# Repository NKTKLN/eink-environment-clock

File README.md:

# 🌱 E-Ink Environment Clock

**E-Ink Environment Clock** is a desk clock on an ESP32-C3 with a 2.9" e-paper panel that shows the time next to indoor CO₂, temperature, humidity and pressure. It is set up from its own web page, publishes its readings to Home Assistant over MQTT and has a local JSON API with no account or key.

The clock has no buttons and no screen you can type on, and it has to stay a clock when the network is gone. So everything is configured from a phone: with no saved network it opens a WPA2 access point and prints the name, password and a QR code on the panel. When a known network disappears it keeps showing the time from its RTC and puts the access point details in a strip at the bottom instead of taking over the screen. The panel itself is slow and ghosts, so it is redrawn only when something visible changes.

## 📦 Dependencies

| Needed for | What | Install |
| --- | --- | --- |
| Building and flashing | [PlatformIO Core](https://docs.platformio.org/en/latest/core/installation/index.html); it downloads ESP-IDF 5.5 and the toolchain itself | `pipx install platformio` |
| Host tests | A C compiler (`gcc` or `clang`) | your package manager |
| Releases | [Commitizen](https://commitizen-tools.github.io/commitizen/), configured in `.cz.toml` | `pipx install commitizen` |

Sensor drivers come from the ESP Component Registry on the first build ([esp-idf-lib](https://esp-idf-lib.readthedocs.io/) `bmp280`, `ds3231`, `mhz19b`, plus `espressif/mdns`).

## 🔩 Hardware

| Part | Model | ESP32-C3 pins |
| --- | --- | --- |
| Microcontroller | ESP32-C3 Super Mini, 4 MB flash | — |
| Display | WeAct Studio 2.9" B/W e-paper, SSD1680, 296×128 | SCK 4, MOSI 6, CS 7, DC 2, RST 3, BUSY 10 |
| Temperature, humidity, pressure | BME280 (BMP280 works without humidity) | I²C SDA 8, SCL 9 |
| Real-time clock | DS3231 | I²C SDA 8, SCL 9 |
| CO₂ | MH-Z19 | UART RX 5 ← sensor TX, TX 1 → sensor RX |
| Status LED | — | 0 |

The pins live in `firmware/src/app_config.h`. GPIO 9 is the BOOT button on the Super Mini and is taken by I²C, which is why the reset below works through power cycles rather than a button.

## 🚀 Flashing

The partition table has two OTA slots and an NVS partition for settings.

> [!IMPORTANT]
> When the board still runs firmware with the old single-app partition table, erase the flash once before the first upload. Later uploads keep the settings.

```sh
cd firmware && pio run -t erase
```

Build and flash over the native USB, then watch the log:

```sh
cd firmware && pio run -t upload && pio device monitor
```

After that, updates go over the air: from GitHub releases or by uploading `.pio/build/esp32-c3-supermini/firmware.bin` on the **System** tab. If a new image fails to start, the bootloader returns to the previous one.

## 📶 Wi-Fi setup

| Situation | What the clock does |
| --- | --- |
| No saved network | Opens the access point `EinkClock-XXXX` and shows the setup screen |
| Saved network unreachable for 30 s | Opens the access point and keeps retrying the saved network; the clock face stays, with the access point details in a strip at the bottom |
| Connected | Shows its address at the bottom for 30 seconds (adjustable, or until removed); the access point stops one minute after connecting |

The access point is WPA2 with a fresh 8-digit password every time it starts, because it also comes up after power cuts when the router boots slower than the clock, and an open network would let anyone nearby point the clock at their own broker. The panel shows the network name, password, a Wi-Fi QR code and `192.168.4.1`. Phones open the setup page on their own: a small DNS server answers every name with that address.

To forget the Wi-Fi and MQTT settings without the web page, plug the clock in three times in a row, unplugging it within five seconds each time. Only power-on resets count, so restarts after an update or a crash never trigger it.

## 🖥️ Web interface

Open `http://<clock-ip>/` or `http://eink-clock-<id>.local/`. English and Russian, light and dark theme, works on a phone. The page is gzipped into the firmware and loads nothing from the internet, so it also works over the setup access point.

| Tab | Contents |
| --- | --- |
| Overview | What the panel shows now, readings, a message for the screen, status |
| Display | Layout, which readings appear and in which order, date and time format, time zone, units, white on black, upside down; a preview rendered by the clock before saving |
| Network | Wi-Fi scan and connection, MQTT broker |
| System | Name, CO₂ threshold, temperature correction, CO₂ calibration, firmware updates, restart and reset |
| Developer | Live device log, log level, API console, raw state |

There is no password on the web interface: it is meant for a home network.

## 🖼️ Screen

| Layout | What it shows |
| --- | --- |
| `classic` | Time and date on the left, enabled readings in a column on the right |
| `clock` | Time and date across the whole panel |
| `co2` | CO₂ in large digits, time and the other readings in a row below |
| `sensors` | Enabled readings in a grid, no clock |

Disabled readings free their space: the column re-centres, one reading is drawn large, and with none left the clock takes the full width. A CO₂ value above the threshold is drawn white on black.

Messages appear as a black strip along the bottom (one line in large type or two in small, cut with "…"), or across the whole panel with `fullscreen`. They can expire after a set time. The panel font is the classic 5×7 bitmap font with Cyrillic letters drawn on the same grid (`firmware/tools/gen_cyrillic_font.py`).

Refresh policy, against ghosting: a full refresh on boot and whenever the kind of screen changes, a partial refresh when the content changes but not more often than every 10 seconds, and a forced full refresh after 10 partial ones.

## 🏠 Home Assistant

Turn on MQTT on the **Network** tab and point it at the broker Home Assistant uses. The clock announces itself through device-based MQTT discovery (Home Assistant 2024.11 or newer) and appears as one device without any YAML.

| Entity | Type |
| --- | --- |
| Temperature, humidity, pressure, CO₂, Wi-Fi signal, uptime | `sensor` |
| CO₂ above threshold | `binary_sensor` |
| Permanent notification, temporary notification | `text` |
| Clear message, restart, calibrate CO₂ | `button` |
| Screen layout | `select` |
| CO₂ threshold, temporary notification time (minutes) | `number` |

There are two kinds of messages. A permanent one stays on the screen until it is removed with the button, from the web interface or through the API. A temporary one disappears by itself: Home Assistant shows it for the time set in its `number` entity, and the web interface asks for the time next to the text.

Readings are published every 30 seconds, and the state right after a setting or a message changes. Automations can set the time per message, or show it on the full screen, through `eink-clock/<id>/notify` (`ttl` 0 means permanent):

```yaml
action: mqtt.publish
data:
  topic: eink-clock/a1b2c3/notify
  payload: '{"text": "Open the window", "ttl": 600, "fullscreen": true}'
```

| Topic under `eink-clock/<id>/` | Direction | Payload |
| --- | --- | --- |
| `state` | out | JSON with all readings, retained |
| `status` | out | `online` / `offline` (last will) |
| `notify` | in | `{"text", "ttl", "fullscreen"}` or plain text |
| `notification/set` | in | plain text, permanent |
| `notification_temp/set` | in | plain text, temporary |
| `notification_time/set` | in | minutes for temporary text, 1…10080 |
| `command` | in | `clear_notification`, `reboot`, `calibrate_co2` |
| `layout/set` | in | `classic`, `clock`, `co2`, `sensors` |
| `co2_threshold/set` | in | 400…5000 |

## ⬆️ Updates and releases

CI publishes a release for every version tag: it builds the firmware with the tag as its version and attaches `firmware.bin`. Tags follow the commitizen format in `.cz.toml` (`1.2.0`, no `v`); a tag with a `-` becomes a pre-release, which the clock does not offer.

```sh
cz bump && git push --follow-tags
```

The clock asks the GitHub API for the latest release once a day and offers it on the **System** tab with its notes and an **Install** button. With automatic updates turned on, a newer release is installed between 03:00 and 05:00 local time, and never while the clock does not know the time. Downloads go over HTTPS with the ESP-IDF certificate bundle.

Images are not signed: HTTPS proves the file came from GitHub, not who uploaded it. Anyone who can publish releases in this repository can ship firmware to clocks with automatic updates on.

Local builds take their version from `.cz.toml`, so a board flashed from the same commit as the latest release does not offer to "update" to it.

## 🔧 Configuration

Everything below is changed in the web interface or with `POST /api/config` (a partial object is enough) and stored in NVS as JSON. Settings survive updates: OTA writes only the app slots, keys the old firmware did not know get their defaults, unknown keys are ignored. CI fails if the NVS partition is moved in `partitions.csv`, because that would wipe them.

| Key | Default | What it is |
| --- | --- | --- |
| `name` | `E-Ink Clock` | Device name, also in Home Assistant |
| `display.language` | `en` | Screen language, `en` or `ru` |
| `display.hour24` | `false` | 24-hour time; the original firmware used 12-hour |
| `display.timezone`, `display.tz_posix` | `Europe/Moscow`, `MSK-3` | Shown name and the POSIX TZ string the firmware uses |
| `display.date_format` | `dmy_text` | `dmy_text` (3 Nov 2026), `weekday`, `dmy_dots`, `iso` |
| `display.show_date` | `true` | Date under the time |
| `display.layout` | `classic` | See the Screen section |
| `display.metrics` | all four, in order | Which readings appear and in which order |
| `display.invert`, `display.rotate180` | `false` | White on black, upside down |
| `display.temp_unit`, `display.pressure_unit` | `c`, `hpa` | Also `f`, `mmhg` |
| `sensors.temp_offset_c` | `-2.3` | Added to the BME280 reading, carried over from the original firmware; limited to ±10 °C |
| `sensors.co2_threshold_ppm` | `1000` | CO₂ alarm: inverted value, LED, Home Assistant binary sensor |
| `sensors.co2_led` | `true` | Blink the LED above the threshold |
| `mqtt.enabled`, `mqtt.host`, `mqtt.port` | `false`, empty, `1883` | Broker; the host may also be a full `mqtt://` URI; TLS (`mqtts://`) is not set up |
| `mqtt.username`, `mqtt.password` | empty | Broker login; the API never returns the password |
| `mqtt.prefix` | empty = `eink-clock/<id>` | Topic prefix |
| `mqtt.discovery`, `mqtt.discovery_prefix` | `true`, `homeassistant` | Home Assistant discovery |
| `update.check` | `true` | Look for a new release once a day |
| `update.auto` | `false` | Install new releases at night; off by default so nothing changes on a clock without the owner asking |

Wi-Fi credentials are set through `POST /api/wifi`, which also reconnects. Fixed timings (sensor interval 30 s, SNTP every 30 minutes, the Wi-Fi fallback above, display refresh limits) are in `firmware/src/app_config.h`.

## 🔌 HTTP API

No keys and no accounts. Everything is JSON except the screen images. CORS is open, so a page or script on another host can call it.

| Method | Path | Purpose |
| --- | --- | --- |
| `GET` | `/api/state` | Readings, time, Wi-Fi, MQTT, message, device info |
| `GET` / `POST` | `/api/config` | Settings; `POST` takes a partial object |
| `GET` | `/api/screen.bmp` | What the panel shows now |
| `POST` | `/api/preview` | Renders unsaved settings, returns a BMP |
| `POST` / `DELETE` | `/api/notify` | Show or clear a message |
| `GET` | `/api/wifi/scan` | Nearby networks |
| `POST` | `/api/wifi` | Save a network and connect |
| `POST` | `/api/co2/calibrate` | MH-Z19 zero point (400 ppm) |
| `POST` | `/api/ota` | Firmware image as the request body |
| `GET` | `/api/update` | Running and latest release, install progress |
| `POST` | `/api/update/check`, `/api/update/install` | Check GitHub now, install the latest release |
| `GET` | `/api/logs?since=N` | Device log after position `N` |
| `POST` | `/api/log-level` | `{"level": "debug", "tag": "*"}` |
| `POST` | `/api/system/reboot`, `/api/system/forget-wifi`, `/api/system/factory-reset` | Maintenance |

Show a message on the screen for an hour:

```sh
curl -X POST http://192.168.1.42/api/notify -d '{"text": "Meeting until 15:00", "ttl": 3600}'
```

## 🛠️ Developer tools

The **Developer** tab keeps the last 12 KB of the device log since boot in RAM and shows it live, with filters by level and text and a download button. It can change the log level per tag until the next restart, send any request to the API and show the raw `/api/state`. The same log is on the USB console via `pio device monitor`.

## 🧪 Tests

Everything that does not touch hardware is plain C and runs on the host: settings and their JSON, settings from older and newer firmware, layouts and text wrapping, the Cyrillic font, messages and their expiry, the power-cycle reset, captive-portal DNS replies, MQTT payloads and commands, version comparison and GitHub release parsing, the log ring buffer. That is 60 test cases. They use cJSON from the ESP-IDF package, so build the firmware once first.

```sh
cd firmware && pio test -e native
```

Set `PREVIEW_DIR` to get every screen the tests render as a PBM image:

```sh
cd firmware && PREVIEW_DIR=/tmp/screens pio test -e native -f test_ui
```

A passing suite says the logic and the drawing are right. It says nothing about Wi-Fi, the radio, the panel driver, the sensors or OTA, which only run on the board. CI runs the build and the tests on every push.

## 🧩 PCB

The KiCad project is in `pcb/eink-environment-clock/`, Gerber files in `pcb/pcb/`. Reference images:

```
images/
├── assembled_board_image.png
├── circuit_image.png
├── pcb_back_image.png
├── pcb_front_image.png
└── schematic_image.png
```

## 🧰 Case

```
3d_model/
├── stp
│   ├── backplate.stp
│   ├── center.stp
│   └── frontplate.stp
├── case.3mf
└── case.m3d
```

## ⚠️ Known issues

* Holes for the **MH-Z19** are too small.
* Some modules (**MH-Z19**) sit too close to the mounting holes, which makes assembly and fastening inconvenient.

## 📁 Source layout

```
firmware/
├── platformio.ini        # firmware env and the host test env
├── partitions.csv        # NVS + two OTA slots
├── web/index.html        # web interface, gzipped into the image at build time
├── test/                 # host unit tests
├── tools/                # web embedding, cJSON for tests, Cyrillic glyph generator
└── src/
    ├── app_main.c        # main loop: sensors, screen choice, refresh policy
    ├── app_config.h      # pins, timings, update repository
    ├── settings*.c       # settings, JSON <-> NVS
    ├── wifi_mgr.c        # station, setup access point, mDNS
    ├── dns_*.c           # captive-portal DNS
    ├── web_server.c      # HTTP API, preview, OTA, logs
    ├── mqtt_ha.c         # MQTT client; ha_*.c build and parse its messages
    ├── updater.c         # GitHub release check and install; release.c parses
    ├── log_*.c           # log capture into a RAM ring buffer
    ├── ui.c              # layouts, messages, setup and system screens
    ├── epd_canvas.c      # 1-bit canvas, UTF-8 text, fonts
    ├── epd_ssd1680.c     # e-paper driver
    └── third_party/      # QR Code generator (Project Nayuki, MIT)
```

The e-paper driver follows the panel vendor's reference code from [WeActStudio.EpaperModule](https://github.com/WeActStudio/WeActStudio.EpaperModule).

## 📜 License

[MIT](./LICENSE).

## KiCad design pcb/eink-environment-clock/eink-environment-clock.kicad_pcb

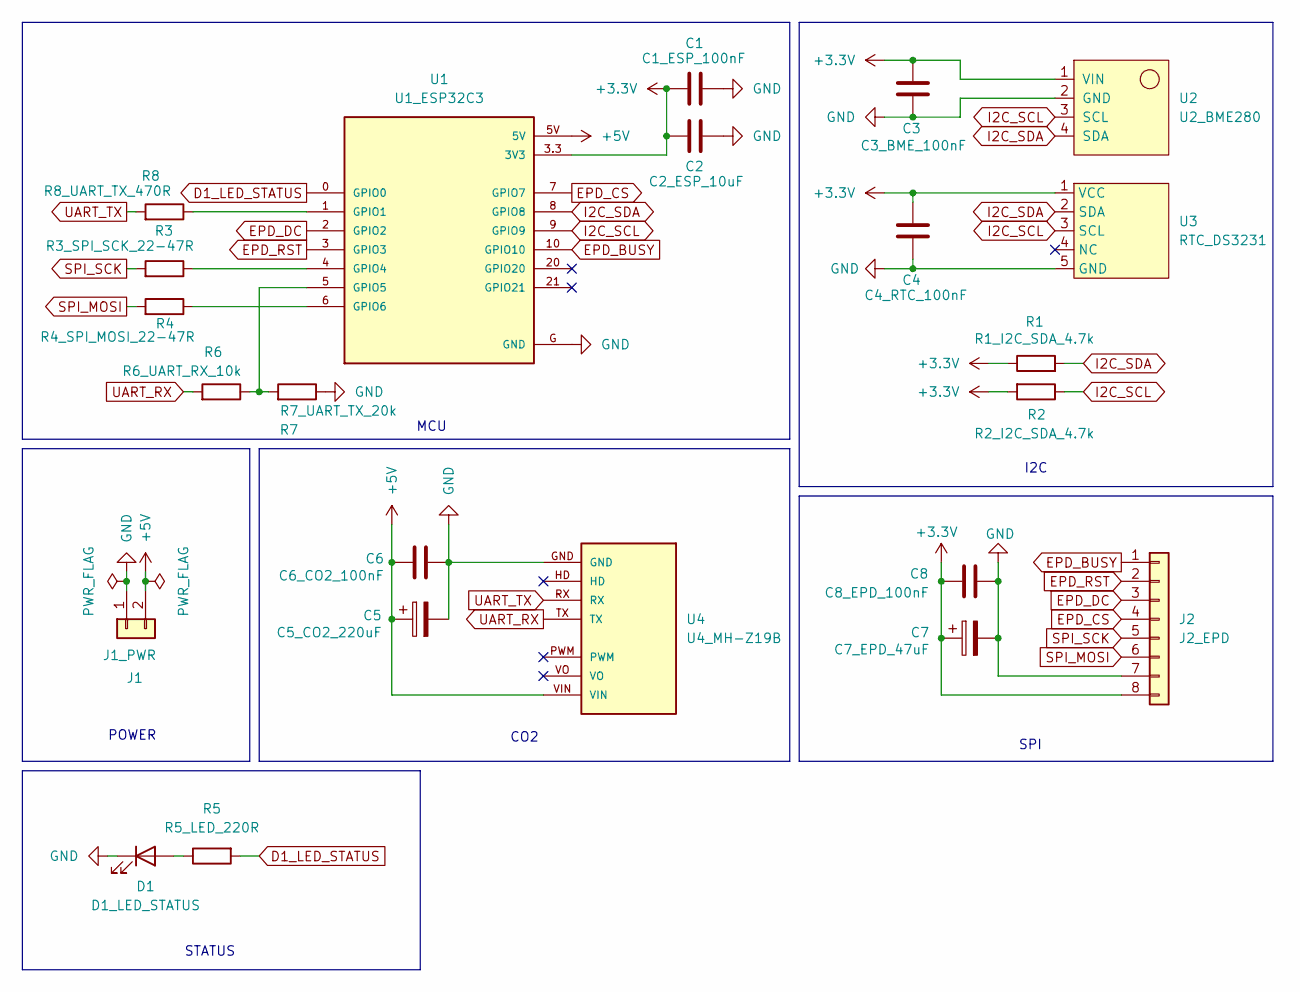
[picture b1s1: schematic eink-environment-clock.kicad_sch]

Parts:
C1: C1_ESP_100nF; C_Disc_D5.0mm_W2.5mm_P2.50mm
C2: C2_ESP_10uF; C_Disc_D5.0mm_W2.5mm_P2.50mm
C3: C3_BME_100nF; C_Disc_D5.0mm_W2.5mm_P2.50mm
C4: C4_RTC_100nF; C_Disc_D5.0mm_W2.5mm_P2.50mm
C5: C5_CO2_220uF; CP_Radial_D8.0mm_P3.50mm
C6: C6_CO2_100nF; C_Disc_D5.0mm_W2.5mm_P2.50mm
C7: C7_EPD_47uF; CP_Radial_D6.3mm_P2.50mm
C8: C8_EPD_100nF; C_Disc_D5.0mm_W2.5mm_P2.50mm
D1: D1_LED_STATUS; LED_D5.0mm
J1: J1_PWR; JST_PH_B2B-PH-K_1x02_P2.00mm_Vertical
J2: J2_EPD; JST_PH_B8B-PH-K_1x08_P2.00mm_Vertical
R1: R1_I2C_SDA_4.7k; R_Axial_DIN0207_L6.3mm_D2.5mm_P7.62mm_Horizontal
R2: R2_I2C_SDA_4.7k; R_Axial_DIN0207_L6.3mm_D2.5mm_P7.62mm_Horizontal
R3: R3_SPI_SCK_22-47R; R_Axial_DIN0207_L6.3mm_D2.5mm_P7.62mm_Horizontal
R4: R4_SPI_MOSI_22-47R; R_Axial_DIN0207_L6.3mm_D2.5mm_P7.62mm_Horizontal
R5: R5_LED_220R; R_Axial_DIN0207_L6.3mm_D2.5mm_P7.62mm_Horizontal
R6: R6_UART_RX_10k; R_Axial_DIN0207_L6.3mm_D2.5mm_P7.62mm_Horizontal
R7: R7_UART_TX_20k; R_Axial_DIN0207_L6.3mm_D2.5mm_P7.62mm_Horizontal
R8: R8_UART_TX_470R; R_Axial_DIN0207_L6.3mm_D2.5mm_P7.62mm_Horizontal
U1: U1_ESP32C3; MODULE_ESP32-C3_SUPERMINI_TH
U2: U2_BME280; module_bme280_alt
U3: RTC_DS3231; DS3231_For_Pi
U4: U4_MH-Z19B; MH-Z19B

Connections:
+3.3V: C1.2, C2.2, C3.1, C4.1, C7.1, C8.2, J2.8, R1.1, R2.2, U1.3.3 (3V3), U2.1 (VIN), U3.1 (VCC)
+5V: C5.1, C6.2, J1.2, U1.5V, U4.VIN
D1_LED_STATUS: R5.2, U1.0 (GPIO0)
EPD_BUSY: J2.1, U1.10 (GPIO10)
EPD_CS: J2.4, U1.7 (GPIO7)
EPD_DC: J2.3, U1.2 (GPIO2)
EPD_RST: J2.2, U1.3 (GPIO3)
GND: C1.1, C2.1, C3.2, C4.2, C5.2, C6.1, C7.2, C8.1, D1.1 (K), J1.1, J2.7, R7.1, U1.G (GND), U2.2 (GND), U3.5 (GND), U4.GND
I2C_SCL: R2.1, U1.9 (GPIO9), U2.3 (SCL), U3.3 (SCL)
I2C_SDA: R1.2, U1.8 (GPIO8), U2.4 (SDA), U3.2 (SDA)
unnamed: D1.2 (A), R5.1
unnamed: R8.1, U1.1 (GPIO1)
unnamed: R3.1, U1.4 (GPIO4)
unnamed: R6.1, R7.2, U1.5 (GPIO5)
unnamed: R4.1, U1.6 (GPIO6)
SPI_MOSI: J2.6, R4.2
SPI_SCK: J2.5, R3.2
UART_RX: R6.2, U4.TX
UART_TX: R8.2, U4.RX

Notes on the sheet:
POWER
CO2
SPI
I2C
STATUS
MCU

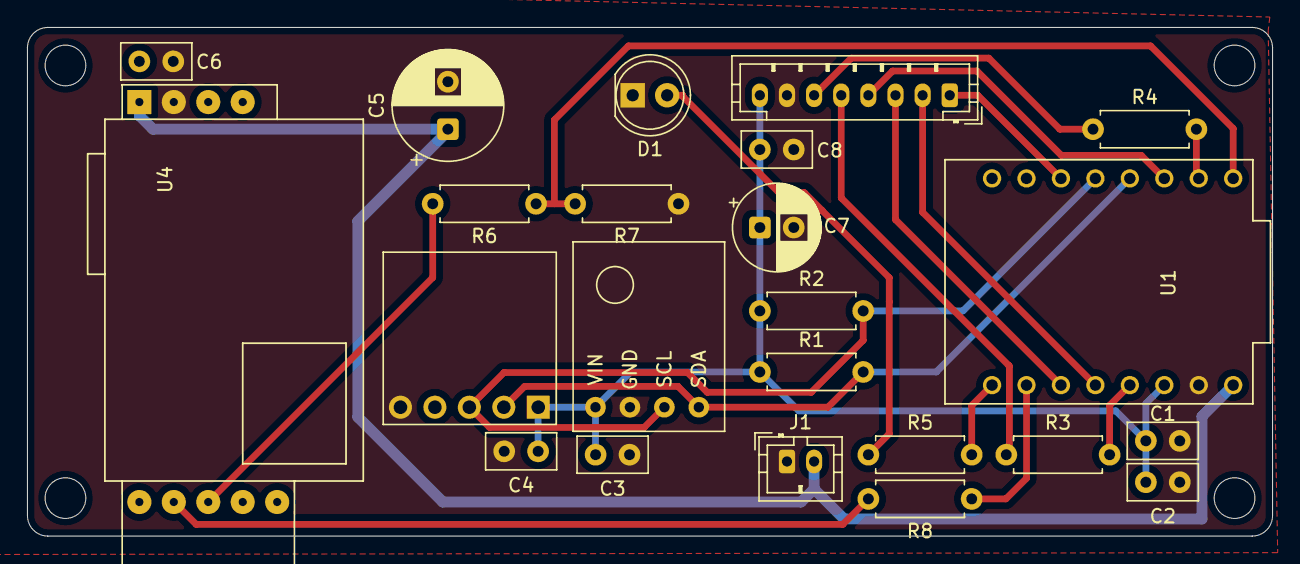
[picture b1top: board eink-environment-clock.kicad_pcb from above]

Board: 2 copper layers, 91.8 x 37.5 mm, 23 parts (0 on the bottom side), 19 nets.

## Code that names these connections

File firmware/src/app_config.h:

#pragma once

/* =====================================================
 * Pin configuration (ESP32-C3 Super Mini)
 * ===================================================== */

/* E-paper display (SPI) */
#define PIN_EPD_DC   2
#define PIN_EPD_RST  3
#define PIN_SPI_SCK  4
#define PIN_SPI_MOSI 6
#define PIN_EPD_CS   7
#define PIN_EPD_BUSY 10

/* I2C bus (BME280 + DS3231) */
#define PIN_I2C_SDA 8
#define PIN_I2C_SCL 9

/* MH-Z19 UART (ESP RX <- sensor TX, ESP TX -> sensor RX) */
#define PIN_MHZ_RX 5
#define PIN_MHZ_TX 1

/* Status LED */
#define PIN_LED 0

/* =====================================================
 * Fixed configuration. Everything a user may want to change (time zone,
 * 12/24 h, units, CO2 threshold, Wi-Fi, MQTT, ...) lives in settings.c and
 * is edited through the web interface.
 * ===================================================== */

#define NTP_SERVER "pool.ntp.org"

/* Firmware updates: GitHub releases of this repository, asset name. */
#define UPDATE_REPO  "NKTKLN/eink-environment-clock"
#define UPDATE_ASSET "firmware.bin"

#define SENSOR_UPDATE_INTERVAL_S 30   /* Read sensors every 30 seconds */
#define TIME_SYNC_INTERVAL_S     1800 /* SNTP resync every 30 minutes */

/* Wi-Fi: how long to try the saved network before opening the setup
 * access point, and how long the AP stays up after a successful
 * connection so the setup page can show the new address. How long the
 * address stays on the screen is a user setting (connect_notice_s). */
#define WIFI_FALLBACK_AP_S     30
#define WIFI_AP_LINGER_S       60

/* Display refresh policy (anti-ghosting):
 *  - full (flashing) refresh on boot and when the screen type changes;
 *  - differential (partial) refresh when the displayed data changes,
 *    but not more often than once in DISPLAY_MIN_UPDATE_PERIOD_S;
 *  - forced full refresh after DISPLAY_FULL_REFRESH_EVERY_N partials. */
#define DISPLAY_MIN_UPDATE_PERIOD_S  10
#define DISPLAY_FULL_REFRESH_EVERY_N 10

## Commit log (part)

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2026-01-01 feat (cirkit image): Add the first version of the connection schematic
2026-01-01 ci(.cz.toml): Add commitizen
2026-01-01 feat(cirkit-image): Add an electrolytic capacitor to the MH-Z19B for stable working
2026-01-02 style(cirkit-image): Update connection schematic
2026-01-11 feat(pcb): Add pcb
2026-01-11 feat(pcb): Add images and update R8
2026-03-12 docs(readme): add README
2026-03-12 docs(readme): update README
    Added PCB design reference images and updated layout.
2026-03-13 feat(sketch): Add v1 sketch
2026-03-13 docs(README.md): Update README with sketch and library information
    Added sections for firmware sketch and libraries used in the project.
2026-03-13 feat(sketch): Add CO2 LED alert
    Updated Wi-Fi credentials and added LED handling for CO2 alert. Adjusted sensor update interval and display text positioning.
2026-03-14 ui(sketch): Fix data row cords
2026-03-14 docs(README.md): Update README to simplify sketch and library sections
    Removed detailed description of sketch functionality and library usage.
2026-03-19 feat(case): Add case model
2026-03-19 docs(README.md): Update PCB paragraph
2026-03-19 feat(sketch): Add dark theme
2026-03-19 fix(case): New version (more durable)
2026-03-26 fix(sensor-display): skip e-paper refresh when data and time are unchanged
2026-03-26 feat(sketch): Add a flag to skip the display refresh
2026-04-02 reafactor(sketch): Refactor sensor and display update logic
2026-04-03 fix(sketch): update logic and timing intervals
2026-04-04 fix(sketch): Update settings
